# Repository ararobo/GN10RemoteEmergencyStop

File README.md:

# GN10RemoteEmergencyStop
PowerCutoffBoard and RemoteSwitchBoard created by Gento Aiba.

This repository contains hardware and firmware for an emergency stop system:
- **PowerCutoffBoard**: A circuit board that cuts off power in emergency situations.
- **RemoteSwitchBoard**: A circuit board that remotely controls switches.

## PowerCutoffBoard
- [Parts List](docs/PowerCutoffBoard_parts.md)
- [KiCad Files-wireless](hardware/PowerCutoffBoard1)
- [KiCad Files-cutoff](hardware/PowerCutoffBoard2)

## RemoteSwitchBoard
- [Parts List](docs/RemoteSwitchBoard_parts.md)
- [KiCad Files](hardware/RemoteSwitchBoard)

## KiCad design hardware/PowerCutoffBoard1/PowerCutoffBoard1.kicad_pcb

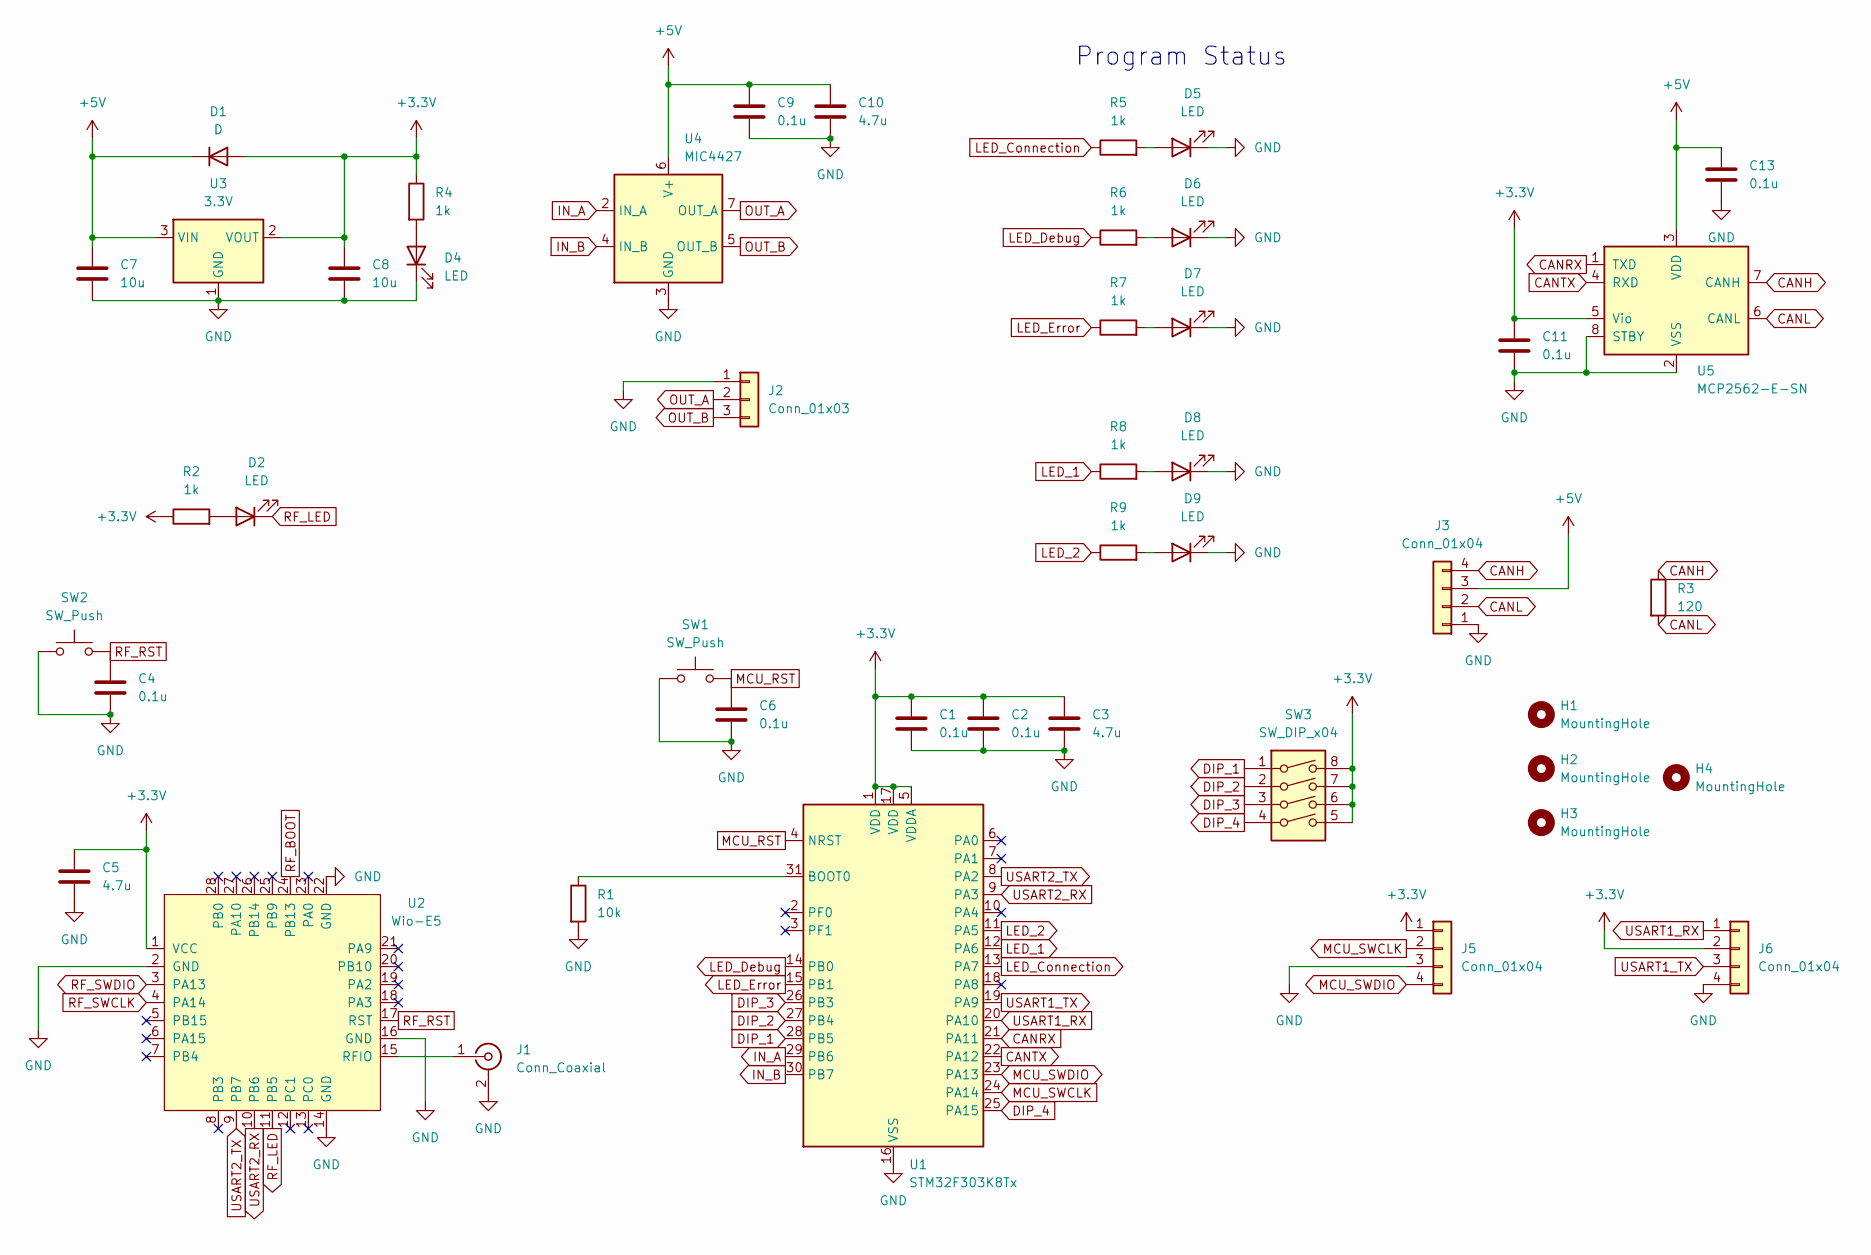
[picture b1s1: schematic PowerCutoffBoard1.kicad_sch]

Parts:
C1, C2, C4, C6, C9, C11, C13: 0.1u; C_0603_1608Metric_Pad1.08x0.95mm_HandSolder
C3, C5, C10: 4.7u; C_0603_1608Metric_Pad1.08x0.95mm_HandSolder
C7, C8: 10u; C_0603_1608Metric_Pad1.08x0.95mm_HandSolder
D1: D; Nexperia_CFP3_SOD-123W
D2, D4, D5, D6, D7, D8, D9: LED; LED_0603_1608Metric_Pad1.05x0.95mm_HandSolder
H1, H2, H3, H4: MountingHole; MountingHole_3.2mm_M3
J1: Conn_Coaxial; SMA_Molex_73251-2120_EdgeMount_Horizontal
J2: Conn_01x03; AMASS_MR30PW-FB_1x03_P3.50mm_Horizontal
J3: Conn_01x04; JST_XH_S4B-XH-A_1x04_P2.50mm_Horizontal
J5, J6: Conn_01x04; JST_XH_B4B-XH-A_1x04_P2.50mm_Vertical
R1: 10k; C_0603_1608Metric_Pad1.08x0.95mm_HandSolder
R2, R4, R5, R6, R7, R8, R9: 1k; C_0603_1608Metric_Pad1.08x0.95mm_HandSolder
R3: 120; R_0603_1608Metric_Pad0.98x0.95mm_HandSolder
SW1, SW2: SW_Push; TVAF
SW3: SW_DIP_x04; SW_DIP_SPSTx04_Slide_Copal_CHS-04B_W7.62mm_P1.27mm
U1: STM32F303K8Tx; LQFP-32_7x7mm_P0.8mm
U2: Wio-E5; LoRa-E5
U3: 3.3V; SOT-223-3_TabPin2
U4: MIC4427; SOIC-8_3.9x4.9mm_P1.27mm
U5: MCP2562-E-SN; SOIC-8_3.9x4.9mm_P1.27mm

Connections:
+3.3V: C1.1, C2.1, C3.1, C5.1, C8.1, C11.1, D1.2 (A), J5.1, J6.2, R2.1, R4.1, SW3.5, SW3.6, SW3.7, SW3.8, U1.1 (VDD), U1.5 (VDDA), U1.17 (VDD), U2.1 (VCC), U3.2 (VOUT), U5.5 (Vio)
+5V: C7.1, C9.1, C10.1, C13.1, D1.1 (K), J3.3, U3.3 (VIN), U4.6 (V+), U5.3 (VDD)
CANH: J3.4, R3.1, U5.7 (CANH)
CANL: J3.2, R3.2, U5.6 (CANL)
CANRX: U1.21 (PA11), U5.1 (TXD)
CANTX: U1.22 (PA12), U5.4 (RXD)
DIP_1: SW3.1, U1.28 (PB5)
DIP_2: SW3.2, U1.27 (PB4)
DIP_3: SW3.3, U1.26 (PB3)
DIP_4: SW3.4, U1.25 (PA15)
GND: C1.2, C2.2, C3.2, C4.2, C5.2, C6.2, C7.2, C8.2, C9.2, C10.2, C11.2, C13.2, D4.1 (K), D5.1 (K), D6.1 (K), D7.1 (K), D8.1 (K), D9.1 (K), J1.2 (Ext), J2.1, J3.1, J5.3, J6.4, R1.2, SW1.1, SW2.1, U1.16 (VSS), U1.32 (VSS), U2.2 (GND), U2.14 (GND), U2.16 (GND), U2.22 (GND), U3.1 (GND), U4.3 (GND), U5.2 (VSS), U5.8 (STBY)
IN_A: U1.29 (PB6), U4.2 (IN_A)
IN_B: U1.30 (PB7), U4.4 (IN_B)
LED_1: R8.1, U1.12 (PA6)
LED_2: R9.1, U1.11 (PA5)
LED_Connection: R5.1, U1.13 (PA7)
LED_Debug: R6.1, U1.14 (PB0)
LED_Error: R7.1, U1.15 (PB1)
MCU_RST: C6.1, SW1.2, U1.4 (NRST)
MCU_SWCLK: J5.2, U1.24 (PA14)
MCU_SWDIO: J5.4, U1.23 (PA13)
unnamed: D2.2 (A), R2.2
unnamed: D4.2 (A), R4.2
unnamed: D5.2 (A), R5.2
unnamed: D6.2 (A), R6.2
unnamed: D7.2 (A), R7.2
unnamed: D8.2 (A), R8.2
unnamed: D9.2 (A), R9.2
unnamed: J1.1 (In), U2.15 (RFIO)
unnamed: R1.1, U1.31 (BOOT0)
OUT_A: J2.2, U4.7 (OUT_A)
OUT_B: J2.3, U4.5 (OUT_B)
RF_BOOT: U2.24 (PB13~)
RF_LED: D2.1 (K), U2.11 (PB5)
RF_RST: C4.1, SW2.2, U2.17 (RST)
RF_SWCLK: U2.4 (PA14)
RF_SWDIO: U2.3 (PA13)
USART1_RX: J6.1, U1.20 (PA10)
USART1_TX: J6.3, U1.19 (PA9)
USART2_RX: U1.9 (PA3), U2.10 (PB6)
USART2_TX: U1.8 (PA2), U2.9 (PB7)

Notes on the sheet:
Program Status

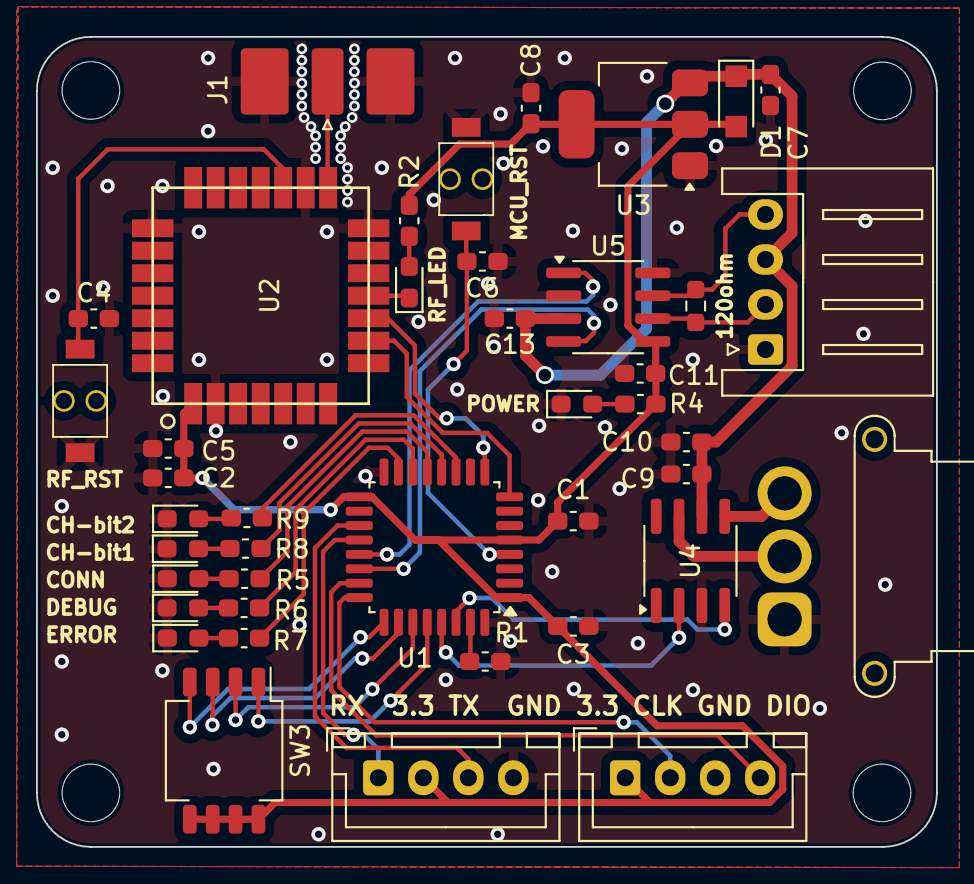
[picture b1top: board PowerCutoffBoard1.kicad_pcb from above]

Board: 2 copper layers, 50.0 x 45.0 mm, 46 parts (0 on the bottom side), 38 nets.

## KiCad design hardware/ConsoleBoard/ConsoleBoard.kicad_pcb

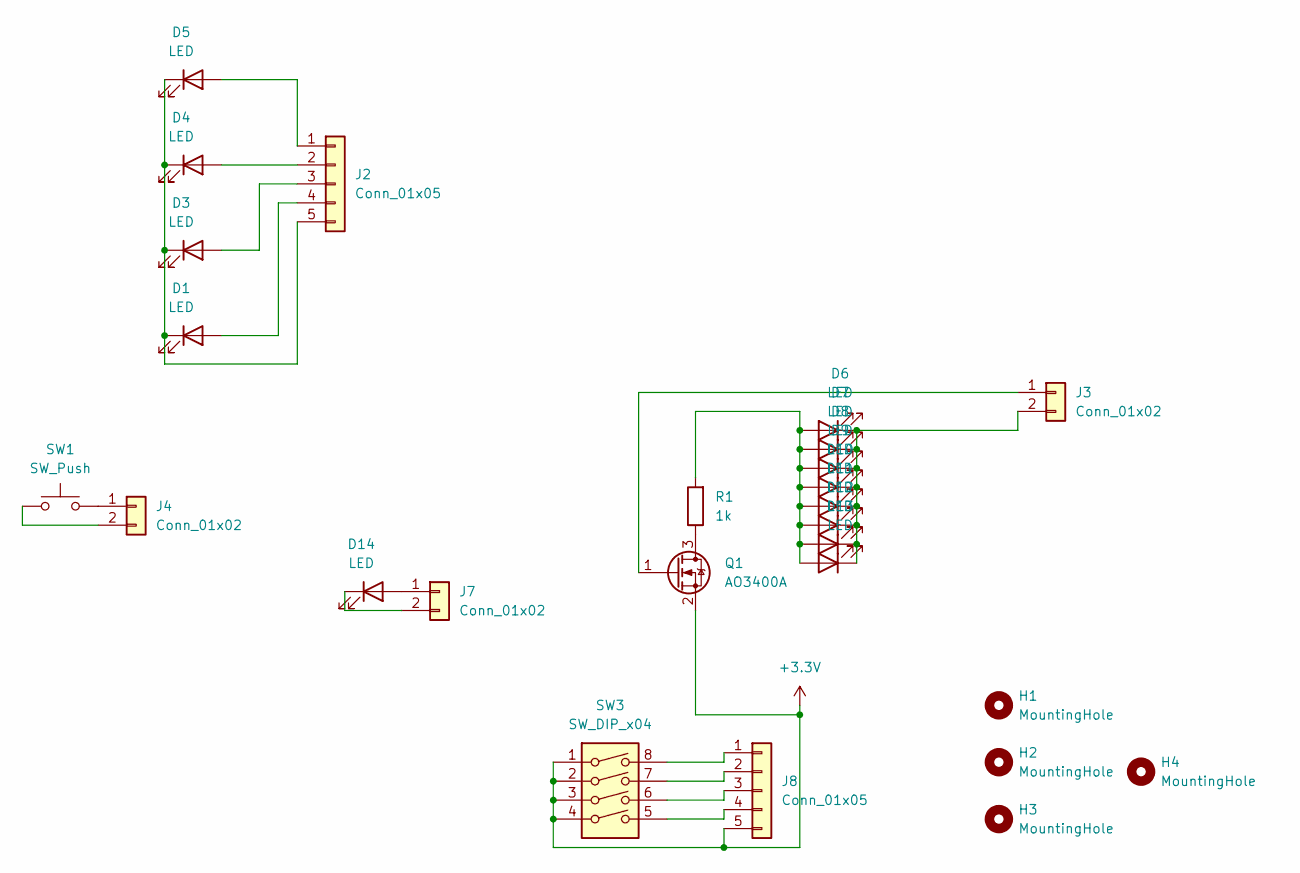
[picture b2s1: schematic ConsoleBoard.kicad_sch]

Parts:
D1, D3, D4, D5, D6, D7, D8, D9, D10, D11, D12, D13, D14: LED; LED_0603_1608Metric_Pad1.05x0.95mm_HandSolder
H1, H2, H3, H4: MountingHole; MountingHole_3.2mm_M3
J2, J8: Conn_01x05; JST_XH_B5B-XH-AM_1x05_P2.50mm_Vertical
J3, J4, J7: Conn_01x02; JST_XH_B2B-XH-A_1x02_P2.50mm_Vertical
Q1: AO3400A; SOT-23
R1: 1k; C_0603_1608Metric_Pad1.08x0.95mm_HandSolder
SW1: SW_Push; TVAF
SW3: SW_DIP_x04; SW_DIP_SPSTx04_Slide_Copal_CHS-04B_W7.62mm_P1.27mm

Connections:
+3.3V: J8.5, Q1.2 (S), SW3.1, SW3.2, SW3.3, SW3.4
unnamed: D1.2 (A), J2.4
unnamed: D1.1 (K), D3.1 (K), D4.1 (K), D5.1 (K), J2.5
unnamed: D3.2 (A), J2.3
unnamed: D4.2 (A), J2.2
unnamed: D5.2 (A), J2.1
unnamed: D6.2 (A), D7.2 (A), D8.2 (A), D9.2 (A), D10.2 (A), D11.2 (A), D12.2 (A), D13.2 (A), R1.2
unnamed: D6.1 (K), D7.1 (K), D8.1 (K), D9.1 (K), D10.1 (K), D11.1 (K), D12.1 (K), D13.1 (K), J3.2
unnamed: D14.2 (A), J7.1
unnamed: D14.1 (K), J7.2
unnamed: J3.1, Q1.1 (G)
unnamed: J4.1, SW1.2
unnamed: J4.2, SW1.1
unnamed: J8.1, SW3.8
unnamed: J8.2, SW3.7
unnamed: J8.3, SW3.6
unnamed: J8.4, SW3.5
unnamed: Q1.3 (D), R1.1

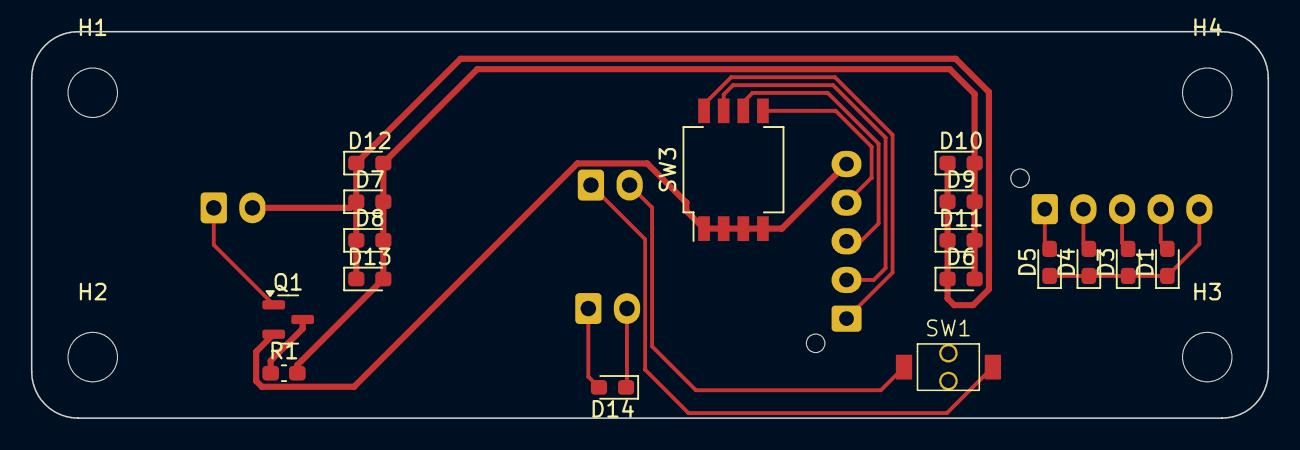
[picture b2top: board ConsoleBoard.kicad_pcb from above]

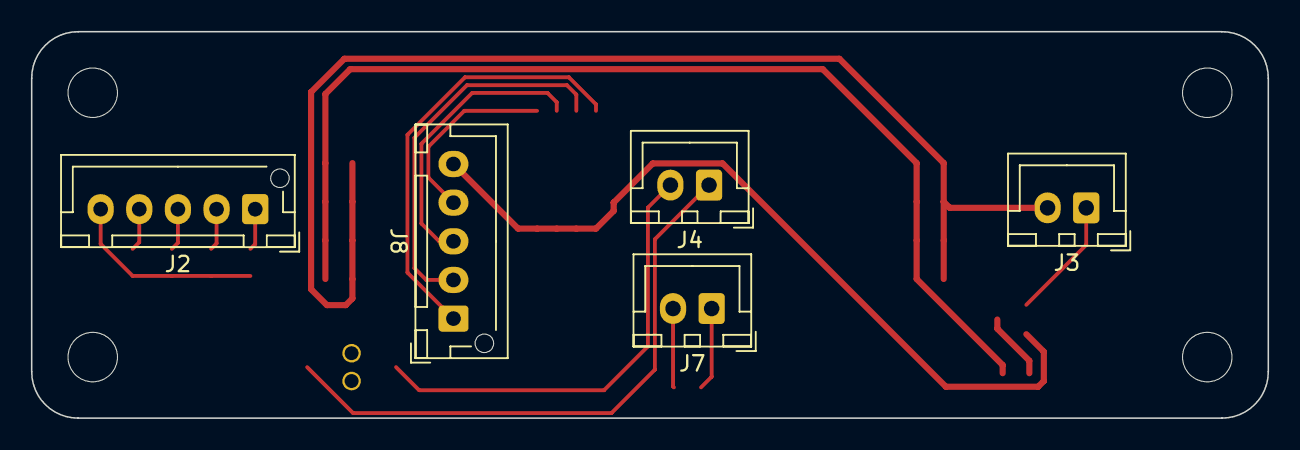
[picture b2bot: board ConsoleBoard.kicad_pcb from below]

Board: 2 copper layers, 80.0 x 25.0 mm, 26 parts (5 on the bottom side), 18 nets.

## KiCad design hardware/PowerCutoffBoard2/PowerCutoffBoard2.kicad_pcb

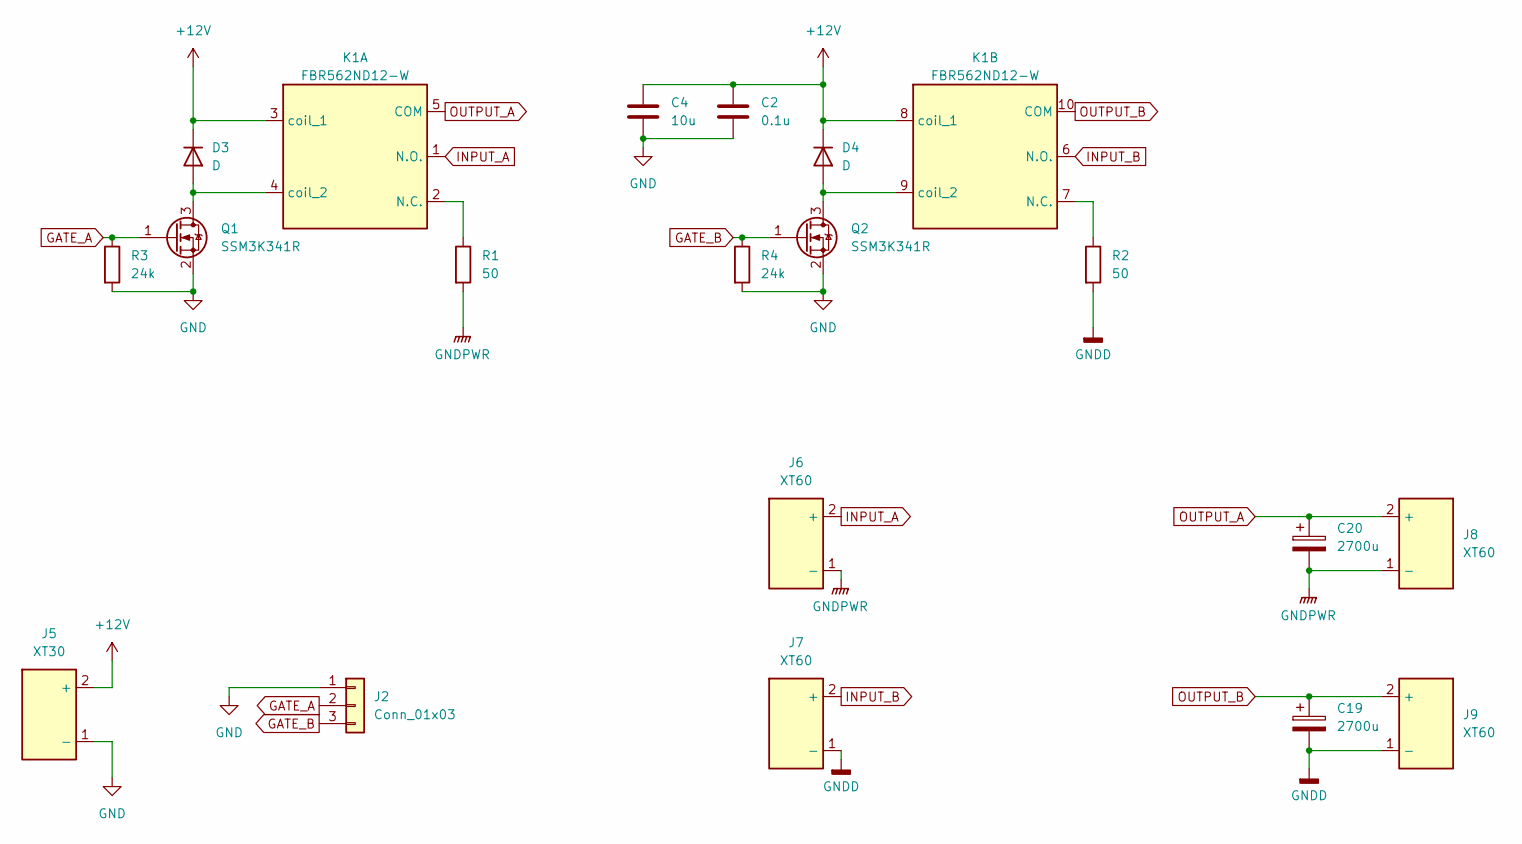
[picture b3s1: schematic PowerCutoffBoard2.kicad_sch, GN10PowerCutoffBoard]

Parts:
C2: 0.1u; C_0603_1608Metric_Pad1.08x0.95mm_HandSolder
C4: 10u; C_0805_2012Metric_Pad1.18x1.45mm_HandSolder
C19, C20: 2700u; CP_Radial_D18.0mm_P7.50mm
D3, D4: D; D_SMA_Handsoldering
J2: Conn_01x03; AMASS_MR30PW-M_1x03_P3.50mm_Horizontal
J5: XT30; AMASS_XT30PW-M_1x02_P2.50mm_Horizontal
J6, J7: XT60; AMASS_XT60-M_1x02_P7.20mm_Vertical
J8, J9: XT60; AMASS_XT60-F_1x02_P7.20mm_Vertical
K1: FBR562ND12-W; FBR562
Q1, Q2: SSM3K341R; SOT-23
R1, R2: 50; R_2010_5025Metric_Pad1.40x2.65mm_HandSolder
R3, R4: 24k; R_0603_1608Metric_Pad0.98x0.95mm_HandSolder

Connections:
+12V: C2.1, C4.1, D3.1 (K), D4.1 (K), J5.2 (+), K1.3 (coil_1), K1.8 (coil_1)
GATE_A: J2.2, Q1.1 (G), R3.1
GATE_B: J2.3, Q2.1 (G), R4.1
GND: C2.2, C4.2, J2.1, J5.1 (-), Q1.2 (S), Q2.2 (S), R3.2, R4.2
GNDD: C19.2, J7.1 (-), J9.1 (-), R2.2
GNDPWR: C20.2, J6.1 (-), J8.1 (-), R1.2
INPUT_A: J6.2 (+), K1.1 (N.O.)
INPUT_B: J7.2 (+), K1.6 (N.O.)
unnamed: D3.2 (A), K1.4 (coil_2), Q1.3 (D)
unnamed: D4.2 (A), K1.9 (coil_2), Q2.3 (D)
unnamed: K1.2 (N.C.), R1.1
unnamed: K1.7 (N.C.), R2.1
OUTPUT_A: C20.1, J8.2 (+), K1.5 (COM)
OUTPUT_B: C19.1, J9.2 (+), K1.10 (COM)

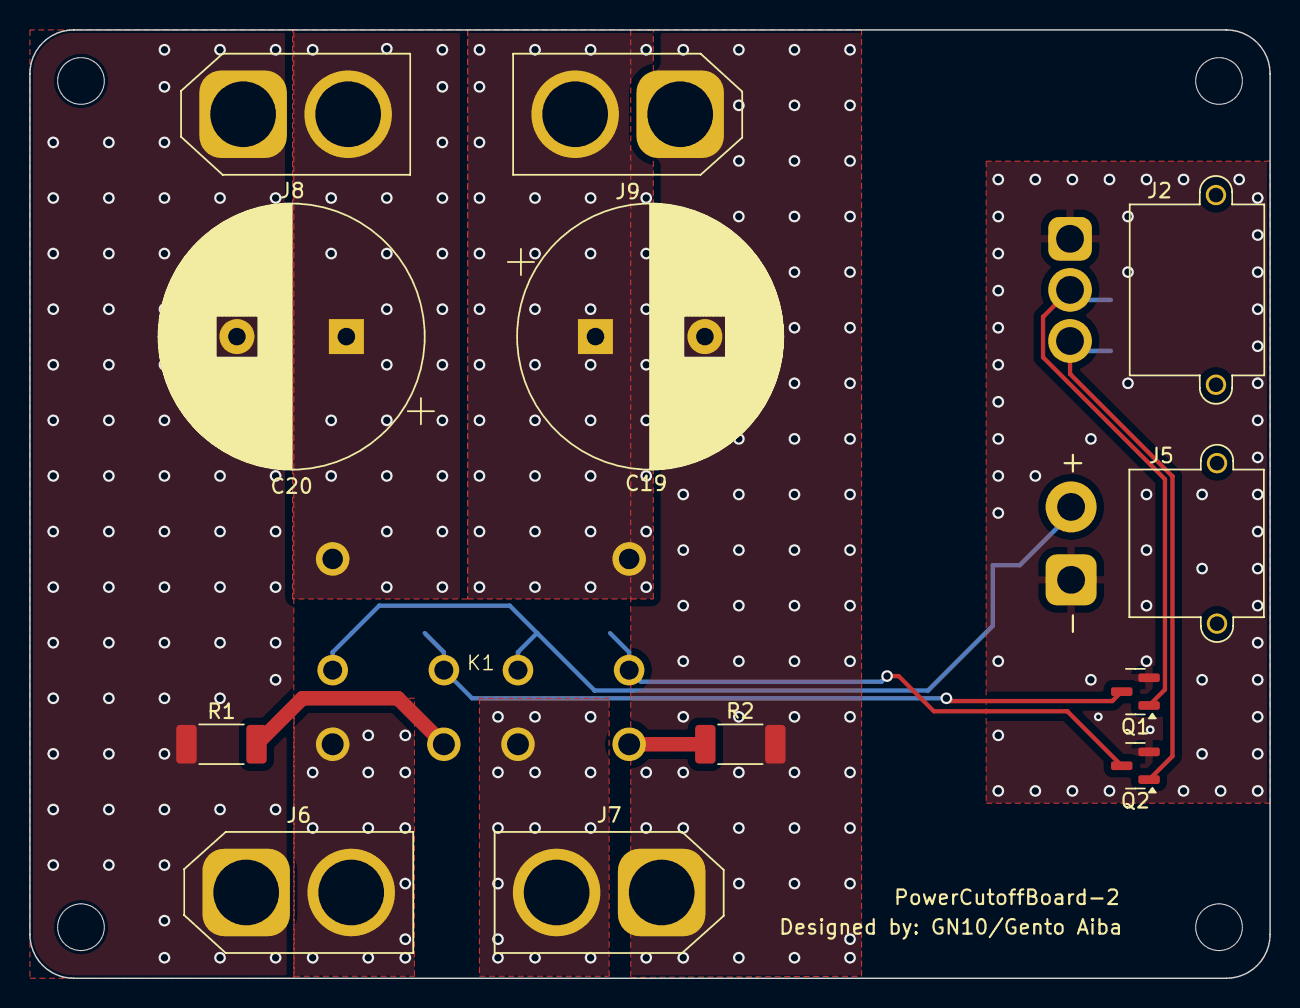
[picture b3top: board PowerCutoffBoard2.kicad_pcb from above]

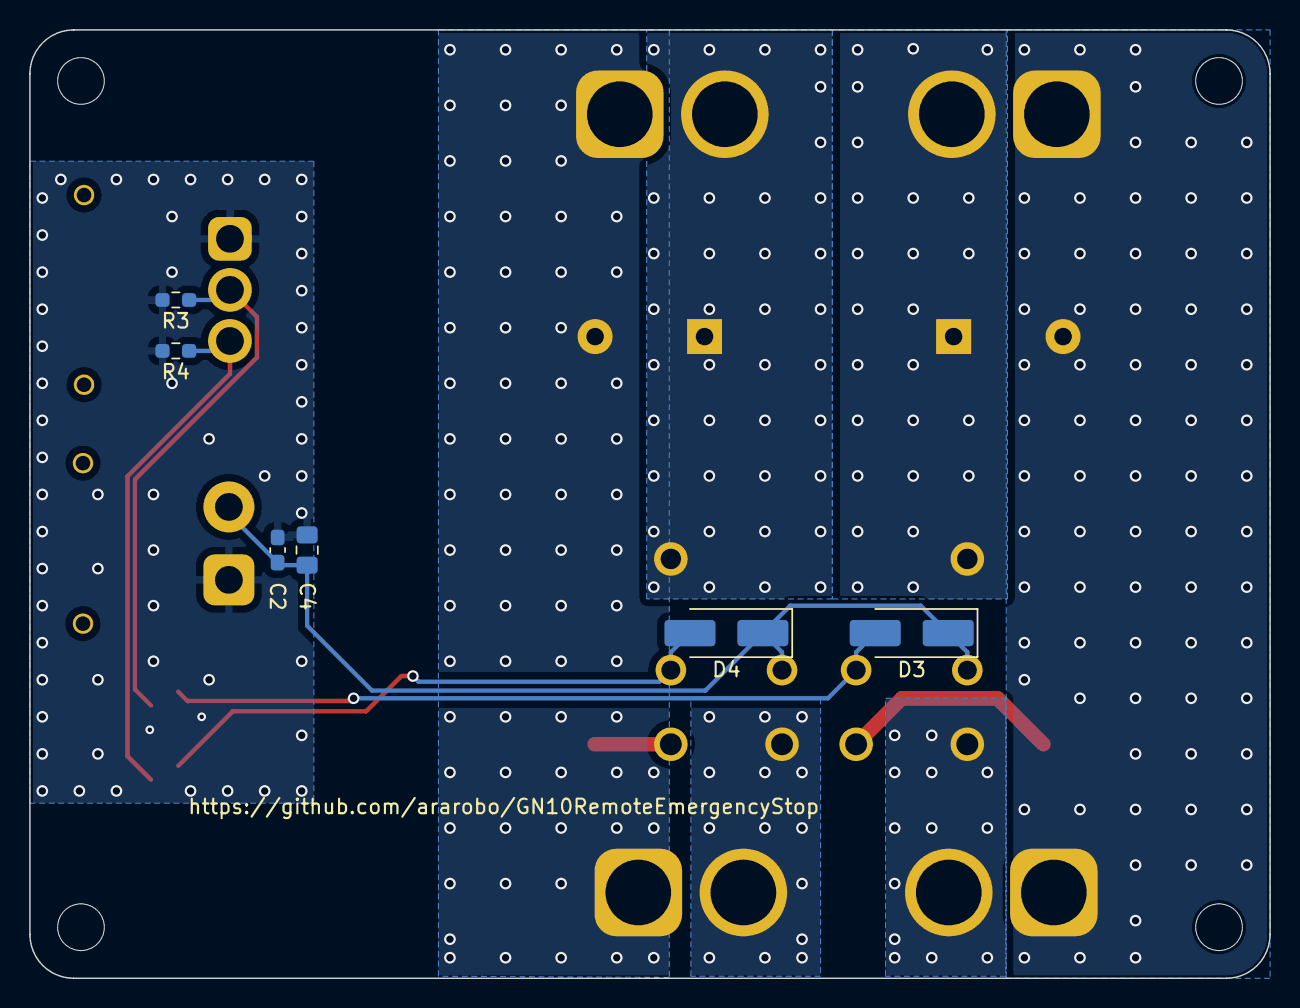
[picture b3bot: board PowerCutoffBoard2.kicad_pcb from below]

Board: 2 copper layers, 85.0 x 65.0 mm, 19 parts (6 on the bottom side), 14 nets.

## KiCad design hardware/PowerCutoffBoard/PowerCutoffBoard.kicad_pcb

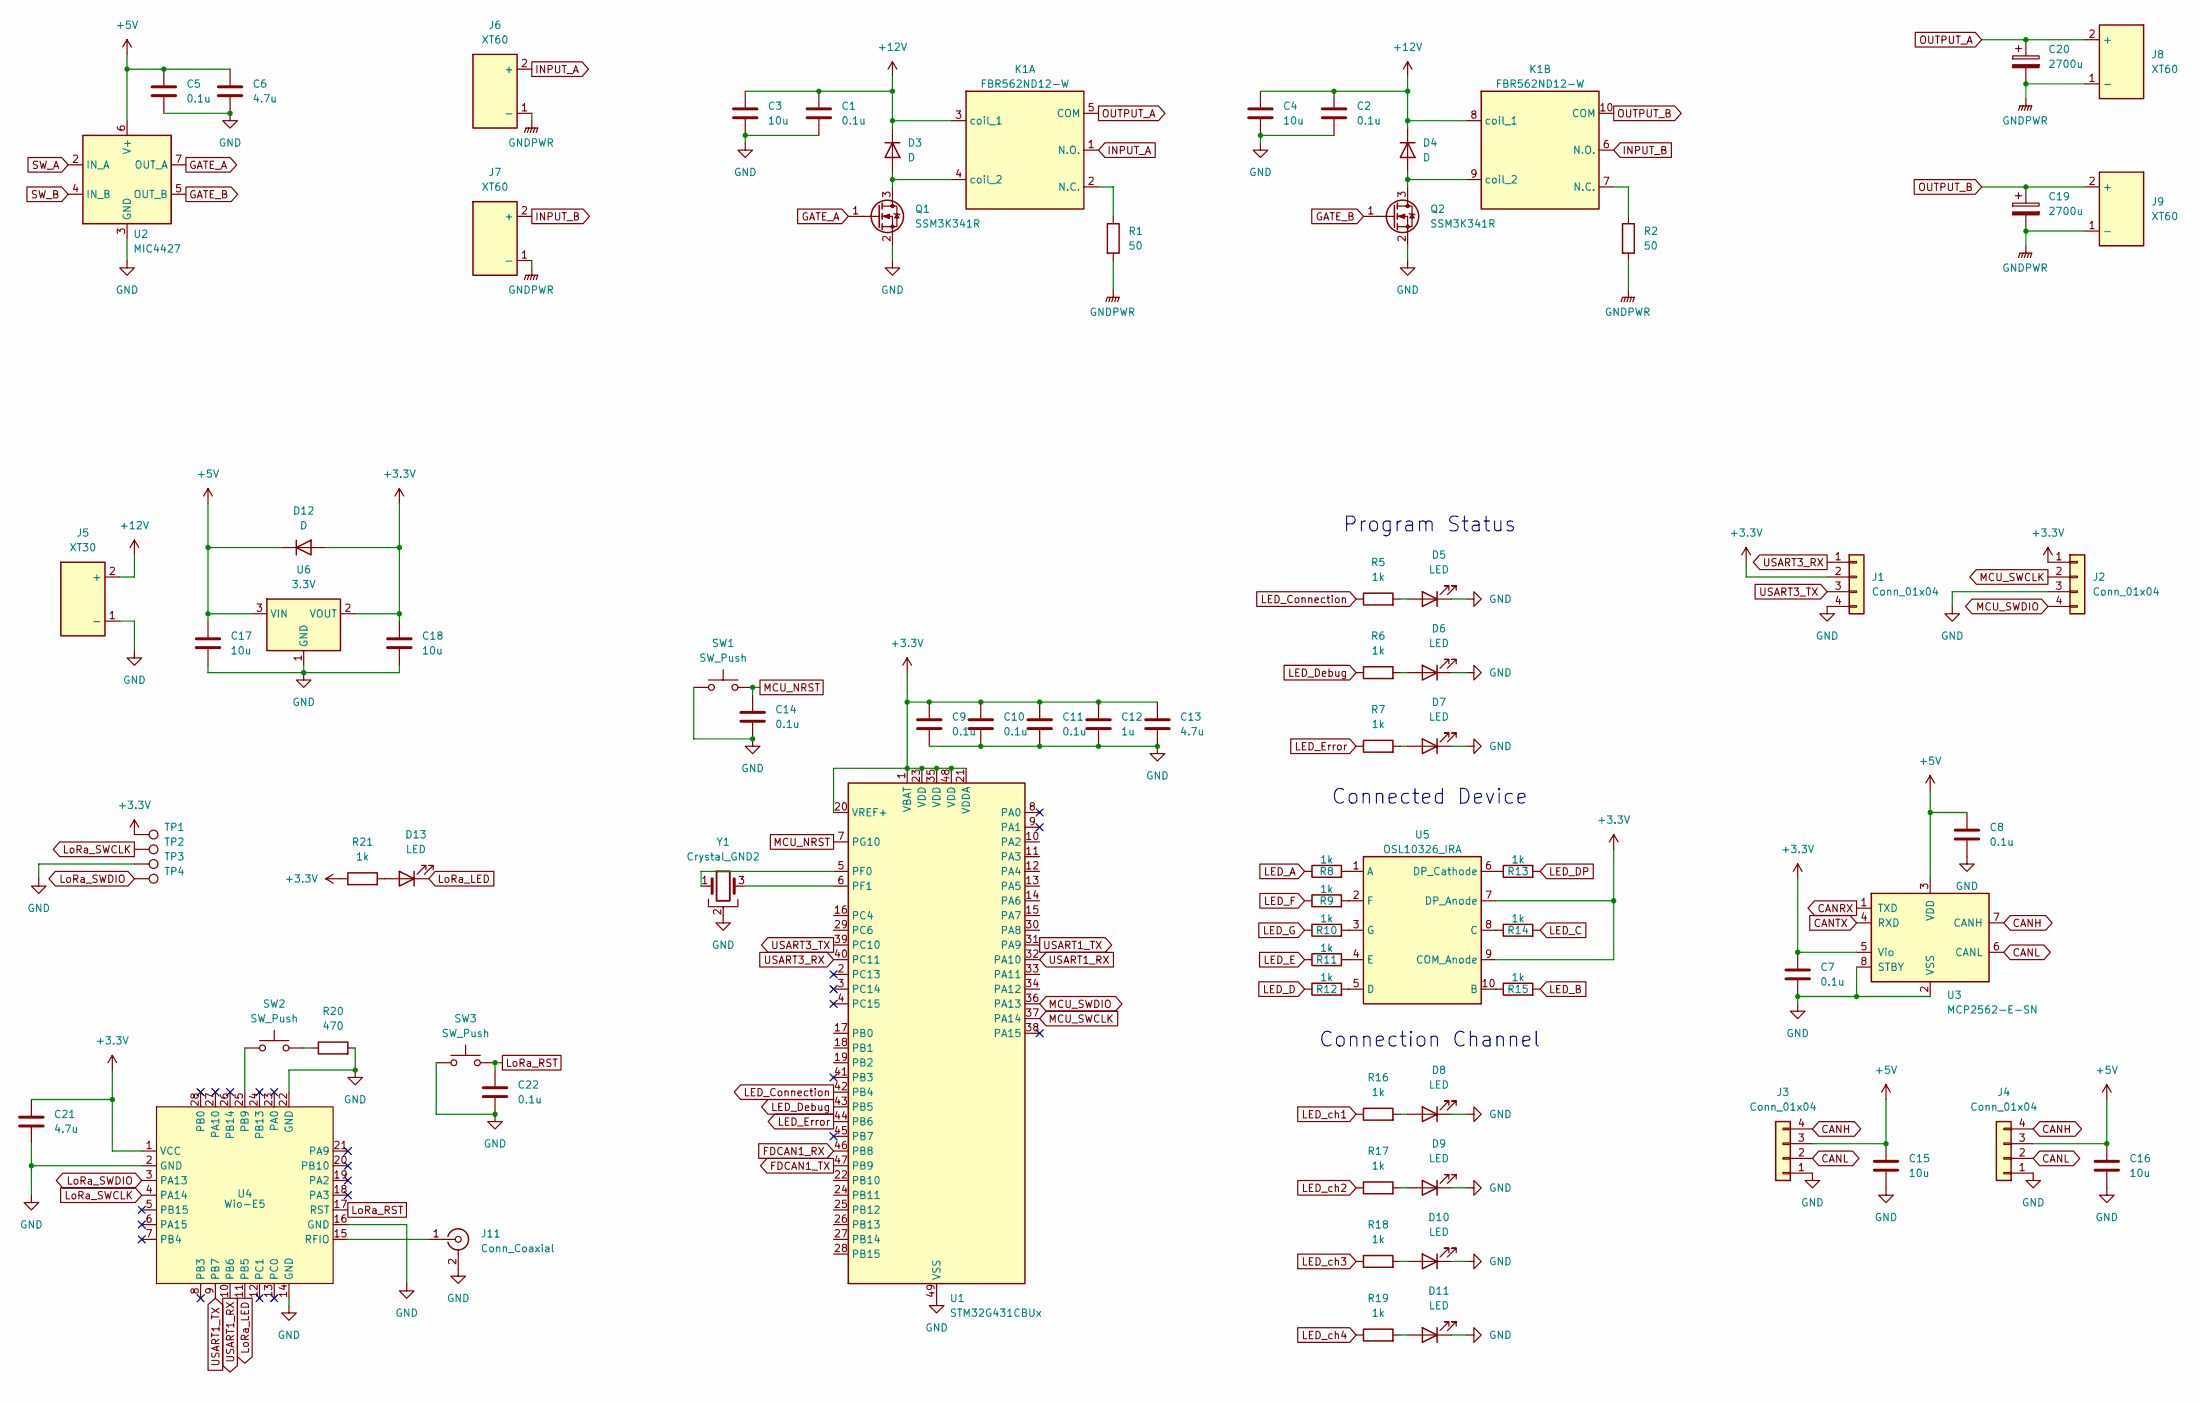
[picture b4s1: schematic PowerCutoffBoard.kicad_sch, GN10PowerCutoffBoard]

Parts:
C1, C2, C5, C7, C8, C14, C22: 0.1u; C_0603_1608Metric_Pad1.08x0.95mm_HandSolder
C3, C4, C15, C16, C17, C18: 10u; C_0805_2012Metric_Pad1.18x1.45mm_HandSolder
C6, C13, C21: 4.7u; C_0603_1608Metric_Pad1.08x0.95mm_HandSolder
C9, C10, C11: 0.1u; C_0402_1005Metric_Pad0.74x0.62mm_HandSolder
C12: 1u; C_0402_1005Metric_Pad0.74x0.62mm_HandSolder
C19, C20: 2700u; CP_Radial_D18.0mm_P7.50mm
D3, D4: D; D_SMA_Handsoldering
D5, D6, D7, D8, D9, D10, D11, D13: LED; LED_0603_1608Metric_Pad1.05x0.95mm_HandSolder
D12: D; D_SOD-123
J1, J2, J3, J4: Conn_01x04; JST_XH_B4B-XH-A_1x04_P2.50mm_Vertical
J5: XT30; AMASS_XT30U-M_1x02_P5.0mm_Vertical
J6, J7: XT60; AMASS_XT60-M_1x02_P7.20mm_Vertical
J8, J9: XT60; AMASS_XT60-F_1x02_P7.20mm_Vertical
J11: Conn_Coaxial; SMA_Molex_73251-2120_EdgeMount_Horizontal
K1: FBR562ND12-W; FBR562
Q1, Q2: SSM3K341R; SOT-23
R1, R2: 50; R_2010_5025Metric_Pad1.40x2.65mm_HandSolder
R5, R6, R7, R8, R9, R10, R11, R12, R13, R14, R15, R16, R17, R18, R19, R21: 1k; C_0603_1608Metric_Pad1.08x0.95mm_HandSolder
R20: 470; C_0603_1608Metric_Pad1.08x0.95mm_HandSolder
SW1, SW2, SW3: SW_Push; TVAF
TP1, TP2, TP3, TP4: TestPoint; TestPoint_Pad_D1.0mm
U1: STM32G431CBUx; QFN-48-1EP_7x7mm_P0.5mm_EP5.6x5.6mm
U2: MIC4427; SOIC-8_3.9x4.9mm_P1.27mm
U3: MCP2562-E-SN; SOIC-8_3.9x4.9mm_P1.27mm
U4: Wio-E5; LoRa-E5
U5: OSL10326_IRA; OSL10326
U6: 3.3V; SOT-223-3_TabPin2
Y1: Crystal_GND2; Resonator_SMD_Murata_CSTxExxV-3Pin_3.0x1.1mm_HandSoldering

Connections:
+3.3V: C7.1, C9.1, C10.1, C11.1, C12.1, C13.1, C18.1, C21.1, D12.2 (A), J1.2, J2.1, R21.1, TP1.1, U1.1 (VBAT), U1.20 (VREF+), U1.21 (VDDA), U1.23 (VDD), U1.35 (VDD), U1.48 (VDD), U3.5 (Vio), U4.1 (VCC), U5.7 (DP_Anode), U5.9 (COM_Anode), U6.2 (VOUT)
+5V: C5.1, C6.1, C8.1, C15.1, C16.1, C17.1, D12.1 (K), J3.3, J4.3, U2.6 (V+), U3.3 (VDD), U6.3 (VIN)
+12V: C1.1, C2.1, C3.1, C4.1, D3.1 (K), D4.1 (K), J5.2 (+), K1.3 (coil_1), K1.8 (coil_1)
CANH: J3.4, J4.4, U3.7 (CANH)
CANL: J3.2, J4.2, U3.6 (CANL)
CANRX: U3.1 (TXD)
CANTX: U3.4 (RXD)
FDCAN1_RX: U1.46 (PB8)
FDCAN1_TX: U1.47 (PB9)
GATE_A: Q1.1 (G), U2.7 (OUT_A)
GATE_B: Q2.1 (G), U2.5 (OUT_B)
GND: C1.2, C2.2, C3.2, C4.2, C5.2, C6.2, C7.2, C8.2, C9.2, C10.2, C11.2, C12.2, C13.2, C14.2, C15.2, C16.2, C17.2, C18.2, C21.2, C22.2, D5.1 (K), D6.1 (K), D7.1 (K), D8.1 (K), D9.1 (K), D10.1 (K), D11.1 (K), J1.4, J2.3, J3.1, J4.1, J5.1 (-), J11.2 (Ext), Q1.2 (S), Q2.2 (S), R20.2, SW1.1, SW3.1, TP3.1, U1.49 (VSS), U2.3 (GND), U3.2 (VSS), U3.8 (STBY), U4.2 (GND), U4.14 (GND), U4.16 (GND), U4.22 (GND), U6.1 (GND), Y1.2
GNDPWR: C19.2, C20.2, J6.1 (-), J7.1 (-), J8.1 (-), J9.1 (-), R1.2, R2.2
INPUT_A: J6.2 (+), K1.1 (N.O.)
INPUT_B: J7.2 (+), K1.6 (N.O.)
LED_A: R8.1
LED_B: R15.2
LED_C: R14.2
LED_Connection: R5.1, U1.42 (PB4)
LED_D: R12.1
LED_DP: R13.2
LED_Debug: R6.1, U1.43 (PB5)
LED_E: R11.1
LED_Error: R7.1, U1.44 (PB6)
LED_F: R9.1
LED_G: R10.1
LED_ch1: R16.1
LED_ch2: R17.1
LED_ch3: R18.1
LED_ch4: R19.1
LoRa_LED: D13.1 (K), U4.11 (PB5)
LoRa_RST: C22.1, SW3.2, U4.17 (RST)
LoRa_SWCLK: TP2.1, U4.4 (PA14)
LoRa_SWDIO: TP4.1, U4.3 (PA13)
MCU_NRST: C14.1, SW1.2, U1.7 (PG10)
MCU_SWCLK: J2.2, U1.37 (PA14)
MCU_SWDIO: J2.4, U1.36 (PA13)
unnamed: D3.2 (A), K1.4 (coil_2), Q1.3 (D)
unnamed: D4.2 (A), K1.9 (coil_2), Q2.3 (D)
unnamed: D5.2 (A), R5.2
unnamed: D6.2 (A), R6.2
unnamed: D7.2 (A), R7.2
unnamed: D8.2 (A), R16.2
unnamed: D9.2 (A), R17.2
unnamed: D10.2 (A), R18.2
unnamed: D11.2 (A), R19.2
unnamed: D13.2 (A), R21.2
unnamed: J11.1 (In), U4.15 (RFIO)
unnamed: K1.2 (N.C.), R1.1
unnamed: K1.7 (N.C.), R2.1
unnamed: R20.1, SW2.2
unnamed: U1.5 (PF0), Y1.1
unnamed: U1.6 (PF1), Y1.3
unnamed: SW2.1, U4.25 (PB9)
unnamed: R8.2, U5.1 (A)
unnamed: R15.1, U5.10 (B)
unnamed: R14.1, U5.8 (C)
unnamed: R12.2, U5.5 (D)
unnamed: R13.1, U5.6 (DP_Cathode)
unnamed: R11.2, U5.4 (E)
unnamed: R9.2, U5.2 (F)
unnamed: R10.2, U5.3 (G)
OUTPUT_A: C20.1, J8.2 (+), K1.5 (COM)
OUTPUT_B: C19.1, J9.2 (+), K1.10 (COM)
SW_A: U2.2 (IN_A)
SW_B: U2.4 (IN_B)
USART1_RX: U1.32 (PA10), U4.10 (PB6)
USART1_TX: U1.31 (PA9), U4.9 (PB7)
USART3_RX: J1.1, U1.40 (PC11)
USART3_TX: J1.3, U1.39 (PC10)

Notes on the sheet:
Connected Device
Connection Channel
Program Status

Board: 2 copper layers, 79 parts (2 on the bottom side), 52 nets, no tracks yet.
